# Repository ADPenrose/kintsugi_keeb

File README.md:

# KINTSUGI
Repository for the kintsugi keyboard.

## Licence
  
Kintsugi is [licenced](LICENSE) under the [Creative Commons Attribution-NonCommercial 4.0 International License](https://creativecommons.org/licenses/by-nc/4.0/).  

This PCB design may be freely reproduced, modified, and manufactured for **PERSONAL USE ONLY** and may not be reproduced in physical form for public sale without the knowledge and permission of me, the desiger of the keyboard. 

That is to say, if you want to run a a public groupbuy, the non-commercial clause can be waived. For that to happen, please contact me at mysticmetromx@gmail.com.

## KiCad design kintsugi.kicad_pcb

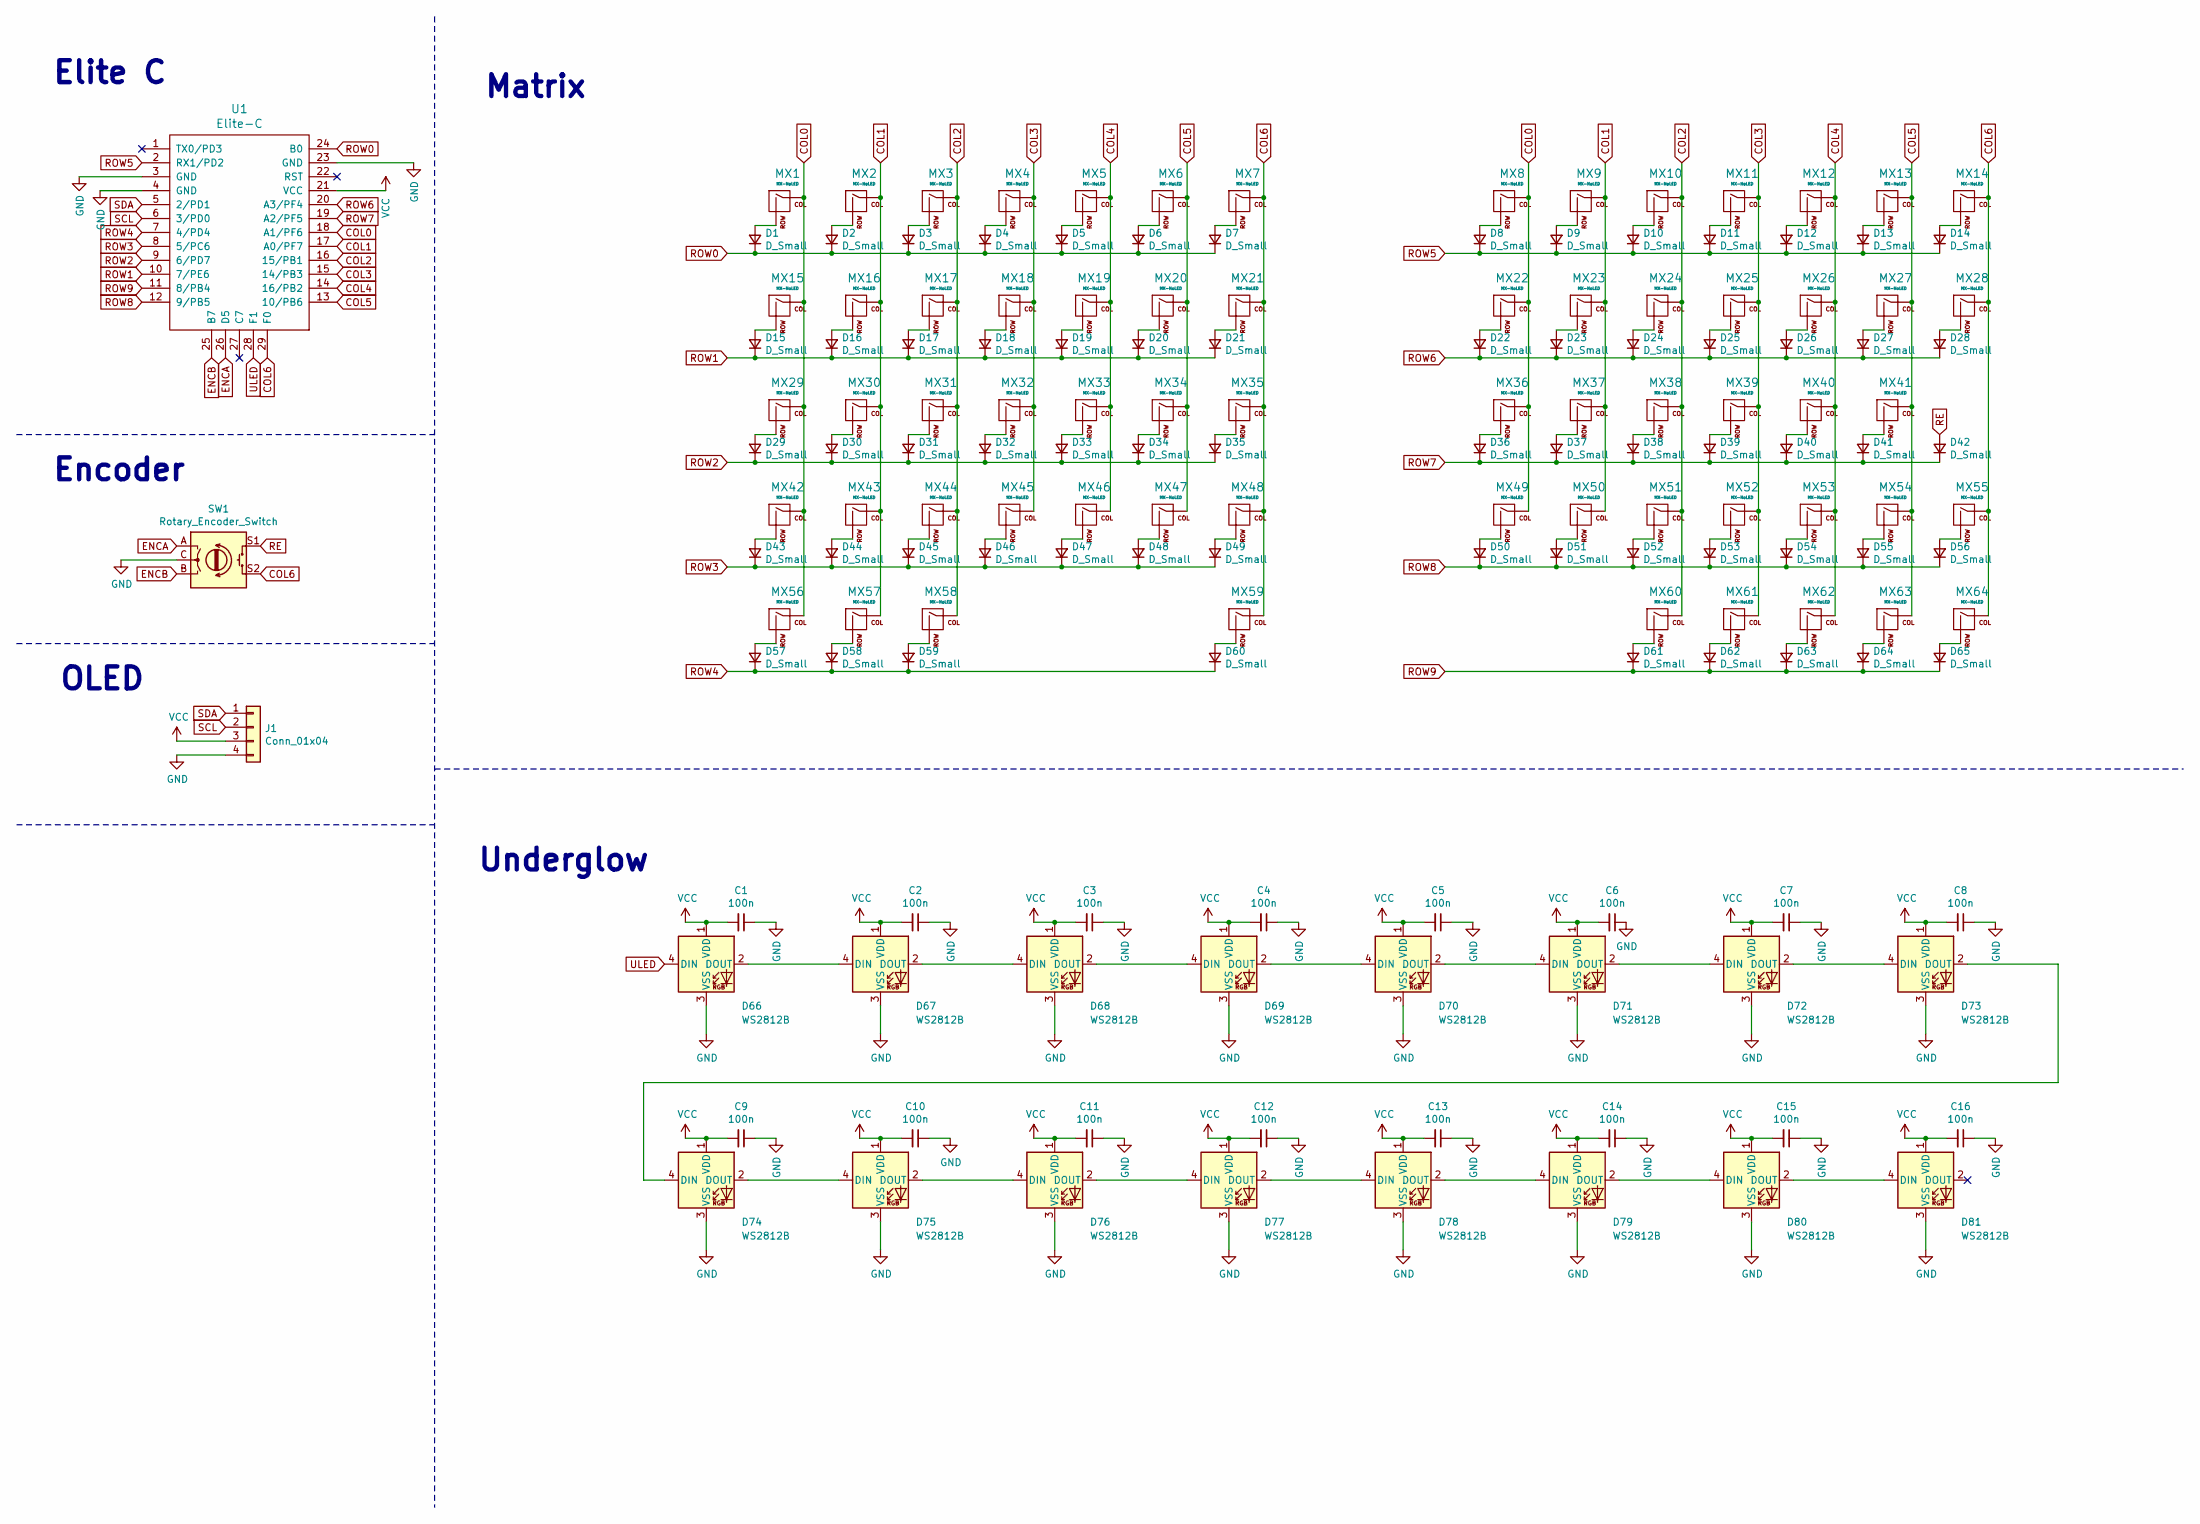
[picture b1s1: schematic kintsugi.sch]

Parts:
C1, C2, C3, C4, C5, C6, C7, C8, C9, C10, C11, C12, C13, C14, C15, C16: 100n; C_0805_2012Metric_Pad1.18x1.45mm_HandSolder
D1, D2, D3, D4, D5, D6, D7, D8, D9, D10, D11, D12, D13, D14, D15, D16, D17, D18, D19, D20, D21, D22, D23, D24, D25, D26, D27, D28, D29, D30, D31, D32, D33, D34, D35, D36, D37, D38, D39, D40, D41, D42, D43, D44, D45, D46, D47, D48, D49, D50, D51, D52, D53, D54, D55, D56, D57, D58, D59, D60, D61, D62, D63, D64, D65: D_Small; Diode-dual-onesided
D66, D67, D68, D69, D70, D71, D72, D73, D74, D75, D76, D77, D78, D79, D80, D81: WS2812B; LED_WS2812B_PLCC4_5.0x5.0mm_P3.2mm
J1: Conn_01x04; PinHeader_1x04_P2.54mm_Vertical
MX1, MX2, MX3, MX4, MX5, MX6, MX7, MX8, MX9, MX10, MX11, MX12, MX13, MX16, MX17, MX18, MX19, MX20, MX21, MX22, MX23, MX24, MX25, MX26, MX27, MX30, MX31, MX32, MX33, MX34, MX35, MX36, MX37, MX38, MX39, MX40, MX43, MX44, MX45, MX46, MX47, MX48, MX49, MX50, MX51, MX52, MX54, MX55, MX62, MX63, MX64: MX-NoLED; MXOnly-1U-Hotswap
MX14: MX-NoLED; MXOnly-2U-Hotswap
MX15, MX28: MX-NoLED; MXOnly-1.5U-Hotswap
MX29, MX53: MX-NoLED; MXOnly-1.75U-Hotswap
MX41, MX42: MX-NoLED; MXOnly-2.25U-Hotswap
MX56, MX57, MX58, MX60, MX61: MX-NoLED; MXOnly-1.25U-Hotswap
MX59: MX-NoLED; MXOnly-6.25U-Hotswap-ReversedStabilizers
SW1: Rotary_Encoder_Switch; RotaryEncoder_Alps_EC11E-Switch_Vertical_H20mm
U1: Elite-C

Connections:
COL0: MX1.1 (COL), MX8.1 (COL), MX15.1 (COL), MX22.1 (COL), MX29.1 (COL), MX36.1 (COL), MX42.1 (COL), MX49.1 (COL), MX56.1 (COL), U1.18 (A1/PF6)
COL1: MX2.1 (COL), MX9.1 (COL), MX16.1 (COL), MX23.1 (COL), MX30.1 (COL), MX37.1 (COL), MX43.1 (COL), MX50.1 (COL), MX57.1 (COL), U1.17 (A0/PF7)
COL2: MX3.1 (COL), MX10.1 (COL), MX17.1 (COL), MX24.1 (COL), MX31.1 (COL), MX38.1 (COL), MX44.1 (COL), MX51.1 (COL), MX58.1 (COL), MX60.1 (COL), U1.16 (15/PB1)
COL3: MX4.1 (COL), MX11.1 (COL), MX18.1 (COL), MX25.1 (COL), MX32.1 (COL), MX39.1 (COL), MX45.1 (COL), MX52.1 (COL), MX61.1 (COL), U1.15 (14/PB3)
COL4: MX5.1 (COL), MX12.1 (COL), MX19.1 (COL), MX26.1 (COL), MX33.1 (COL), MX40.1 (COL), MX46.1 (COL), MX53.1 (COL), MX62.1 (COL), U1.14 (16/PB2)
COL5: MX6.1 (COL), MX13.1 (COL), MX20.1 (COL), MX27.1 (COL), MX34.1 (COL), MX41.1 (COL), MX47.1 (COL), MX54.1 (COL), MX63.1 (COL), U1.13 (10/PB6)
COL6: MX7.1 (COL), MX14.1 (COL), MX21.1 (COL), MX28.1 (COL), MX35.1 (COL), MX48.1 (COL), MX55.1 (COL), MX59.1 (COL), MX64.1 (COL), SW1.S2, U1.29 (F0)
ENCA: SW1.A, U1.26 (D5)
ENCB: SW1.B, U1.25 (B7)
GND: C1.1, C2.1, C3.1, C4.1, C5.1, C6.1, C7.1, C8.1, C9.1, C10.1, C11.1, C12.1, C13.1, C14.1, C15.1, C16.1, D66.3 (VSS), D67.3 (VSS), D68.3 (VSS), D69.3 (VSS), D70.3 (VSS), D71.3 (VSS), D72.3 (VSS), D73.3 (VSS), D74.3 (VSS), D75.3 (VSS), D76.3 (VSS), D77.3 (VSS), D78.3 (VSS), D79.3 (VSS), D80.3 (VSS), D81.3 (VSS), J1.4, SW1.C, U1.3 (GND), U1.4 (GND), U1.23 (GND)
unnamed: D1.2 (A), MX1.2 (ROW)
unnamed: D2.2 (A), MX2.2 (ROW)
unnamed: D3.2 (A), MX3.2 (ROW)
unnamed: D4.2 (A), MX4.2 (ROW)
unnamed: D5.2 (A), MX5.2 (ROW)
unnamed: D6.2 (A), MX6.2 (ROW)
unnamed: D7.2 (A), MX7.2 (ROW)
unnamed: D8.2 (A), MX8.2 (ROW)
unnamed: D9.2 (A), MX9.2 (ROW)
unnamed: D10.2 (A), MX10.2 (ROW)
unnamed: D11.2 (A), MX11.2 (ROW)
unnamed: D12.2 (A), MX12.2 (ROW)
unnamed: D13.2 (A), MX13.2 (ROW)
unnamed: D14.2 (A), MX14.2 (ROW)
unnamed: D15.2 (A), MX15.2 (ROW)
unnamed: D16.2 (A), MX16.2 (ROW)
unnamed: D17.2 (A), MX17.2 (ROW)
unnamed: D18.2 (A), MX18.2 (ROW)
unnamed: D19.2 (A), MX19.2 (ROW)
unnamed: D20.2 (A), MX20.2 (ROW)
unnamed: D21.2 (A), MX21.2 (ROW)
unnamed: D22.2 (A), MX22.2 (ROW)
unnamed: D23.2 (A), MX23.2 (ROW)
unnamed: D24.2 (A), MX24.2 (ROW)
unnamed: D25.2 (A), MX25.2 (ROW)
unnamed: D26.2 (A), MX26.2 (ROW)
unnamed: D27.2 (A), MX27.2 (ROW)
unnamed: D28.2 (A), MX28.2 (ROW)
unnamed: D29.2 (A), MX29.2 (ROW)
unnamed: D30.2 (A), MX30.2 (ROW)
unnamed: D31.2 (A), MX31.2 (ROW)
unnamed: D32.2 (A), MX32.2 (ROW)
unnamed: D33.2 (A), MX33.2 (ROW)
unnamed: D34.2 (A), MX34.2 (ROW)
unnamed: D35.2 (A), MX35.2 (ROW)
unnamed: D36.2 (A), MX36.2 (ROW)
unnamed: D37.2 (A), MX37.2 (ROW)
unnamed: D38.2 (A), MX38.2 (ROW)
unnamed: D39.2 (A), MX39.2 (ROW)
unnamed: D40.2 (A), MX40.2 (ROW)
unnamed: D41.2 (A), MX41.2 (ROW)
unnamed: D43.2 (A), MX42.2 (ROW)
unnamed: D44.2 (A), MX43.2 (ROW)
unnamed: D45.2 (A), MX44.2 (ROW)
unnamed: D46.2 (A), MX45.2 (ROW)
unnamed: D47.2 (A), MX46.2 (ROW)
unnamed: D48.2 (A), MX47.2 (ROW)
unnamed: D49.2 (A), MX48.2 (ROW)
unnamed: D50.2 (A), MX49.2 (ROW)
unnamed: D51.2 (A), MX50.2 (ROW)
unnamed: D52.2 (A), MX51.2 (ROW)
unnamed: D53.2 (A), MX52.2 (ROW)
unnamed: D54.2 (A), MX53.2 (ROW)
unnamed: D55.2 (A), MX54.2 (ROW)
unnamed: D56.2 (A), MX55.2 (ROW)
unnamed: D57.2 (A), MX56.2 (ROW)
unnamed: D58.2 (A), MX57.2 (ROW)
unnamed: D59.2 (A), MX58.2 (ROW)
unnamed: D60.2 (A), MX59.2 (ROW)
unnamed: D61.2 (A), MX60.2 (ROW)
unnamed: D62.2 (A), MX61.2 (ROW)
unnamed: D63.2 (A), MX62.2 (ROW)
unnamed: D64.2 (A), MX63.2 (ROW)
unnamed: D65.2 (A), MX64.2 (ROW)
unnamed: D66.2 (DOUT), D67.4 (DIN)
unnamed: D67.2 (DOUT), D68.4 (DIN)
unnamed: D68.2 (DOUT), D69.4 (DIN)
unnamed: D69.2 (DOUT), D70.4 (DIN)
unnamed: D70.2 (DOUT), D71.4 (DIN)
unnamed: D71.2 (DOUT), D72.4 (DIN)
unnamed: D72.2 (DOUT), D73.4 (DIN)
unnamed: D73.2 (DOUT), D74.4 (DIN)
unnamed: D74.2 (DOUT), D75.4 (DIN)
unnamed: D75.2 (DOUT), D76.4 (DIN)
unnamed: D76.2 (DOUT), D77.4 (DIN)
unnamed: D77.2 (DOUT), D78.4 (DIN)
unnamed: D78.2 (DOUT), D79.4 (DIN)
unnamed: D79.2 (DOUT), D80.4 (DIN)
unnamed: D80.2 (DOUT), D81.4 (DIN)
RE: D42.2 (A), SW1.S1
ROW0: D1.1 (K), D2.1 (K), D3.1 (K), D4.1 (K), D5.1 (K), D6.1 (K), D7.1 (K), U1.24 (B0)
ROW1: D15.1 (K), D16.1 (K), D17.1 (K), D18.1 (K), D19.1 (K), D20.1 (K), D21.1 (K), U1.10 (7/PE6)
ROW2: D29.1 (K), D30.1 (K), D31.1 (K), D32.1 (K), D33.1 (K), D34.1 (K), D35.1 (K), U1.9 (6/PD7)
ROW3: D43.1 (K), D44.1 (K), D45.1 (K), D46.1 (K), D47.1 (K), D48.1 (K), D49.1 (K), U1.8 (5/PC6)
ROW4: D57.1 (K), D58.1 (K), D59.1 (K), D60.1 (K), U1.7 (4/PD4)
ROW5: D8.1 (K), D9.1 (K), D10.1 (K), D11.1 (K), D12.1 (K), D13.1 (K), D14.1 (K), U1.2 (RX1/PD2)
ROW6: D22.1 (K), D23.1 (K), D24.1 (K), D25.1 (K), D26.1 (K), D27.1 (K), D28.1 (K), U1.20 (A3/PF4)
ROW7: D36.1 (K), D37.1 (K), D38.1 (K), D39.1 (K), D40.1 (K), D41.1 (K), D42.1 (K), U1.19 (A2/PF5)
ROW8: D50.1 (K), D51.1 (K), D52.1 (K), D53.1 (K), D54.1 (K), D55.1 (K), D56.1 (K), U1.12 (9/PB5)
ROW9: D61.1 (K), D62.1 (K), D63.1 (K), D64.1 (K), D65.1 (K), U1.11 (8/PB4)
SCL: J1.2, U1.6 (3/PD0)
SDA: J1.1, U1.5 (2/PD1)
ULED: D66.4 (DIN), U1.28 (F1)
VCC: C1.2, C2.2, C3.2, C4.2, C5.2, C6.2, C7.2, C8.2, C9.2, C10.2, C11.2, C12.2, C13.2, C14.2, C15.2, C16.2, D66.1 (VDD), D67.1 (VDD), D68.1 (VDD), D69.1 (VDD), D70.1 (VDD), D71.1 (VDD), D72.1 (VDD), D73.1 (VDD), D74.1 (VDD), D75.1 (VDD), D76.1 (VDD), D77.1 (VDD), D78.1 (VDD), D79.1 (VDD), D80.1 (VDD), D81.1 (VDD), J1.3, U1.21 (VCC)

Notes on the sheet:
Elite C
Encoder
OLED
Underglow
Matrix

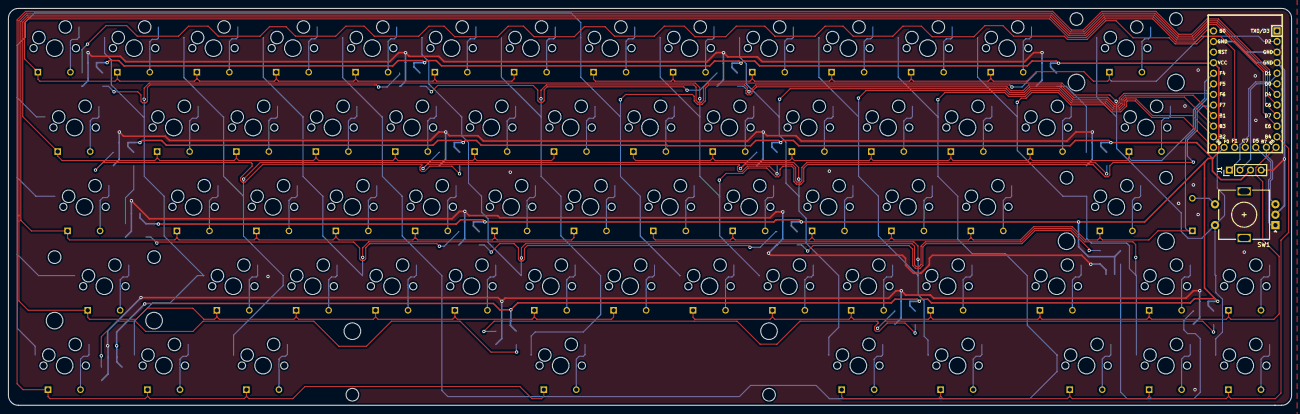
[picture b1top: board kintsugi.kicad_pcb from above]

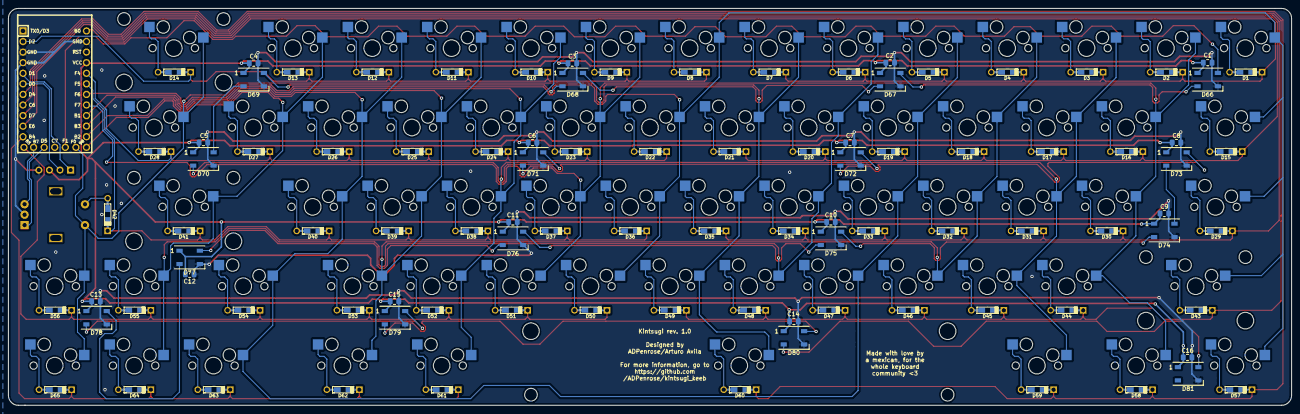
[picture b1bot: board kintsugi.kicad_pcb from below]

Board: 2 copper layers, 308.0 x 95.2 mm, 164 parts (98 on the bottom side), 104 nets.

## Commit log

2021-08-29 Add submodules
2021-08-29 Added last submodule
2021-08-29 Added the random keyboard parts library.
2021-08-29 First commit
    Added Elite C and initial switch and diodes matrix symbols.
2021-09-04 Footprints added
    First revision of the schematic finished and footprints added.
2021-09-04 Created LICENSE
2021-09-04 Update README.md
    Added license to readme.
2021-09-04 Updated README and images
    Title changed and images of the layout and matrix added.
2021-09-05 Routing started
    Began routing rows and columns
2021-09-06 Columns and rows connected
    Switches connected to their respective row and column
2021-09-06 Old routing
    Created a new branch to save the original idea
2021-09-06 Deleted old routing
    Fresh start
2021-09-07 Routed rows and first three columns
    Began routing the new pcb.
2021-09-08 Re-routed rows, cols, oled and encoder
    Routed for the third time the board, rows in front, cols in back.
2021-09-08 Began routing leds
    Started with the underglows routing
2021-09-11 Routed first 5 rows
    Finished routing leds and first 5 rows
2021-09-11 Finished routing and gnd fill
    First revision completed, waiting for review
2021-09-11 Added silkscreen logos
    Almost there
2021-09-12 Gerber files generated
    I think this is where it ends
2021-11-19 Case
    Added proto case files
2022-06-10 Added fixed case files. Pending review.
2022-06-16 Addeds v2 of the case.
